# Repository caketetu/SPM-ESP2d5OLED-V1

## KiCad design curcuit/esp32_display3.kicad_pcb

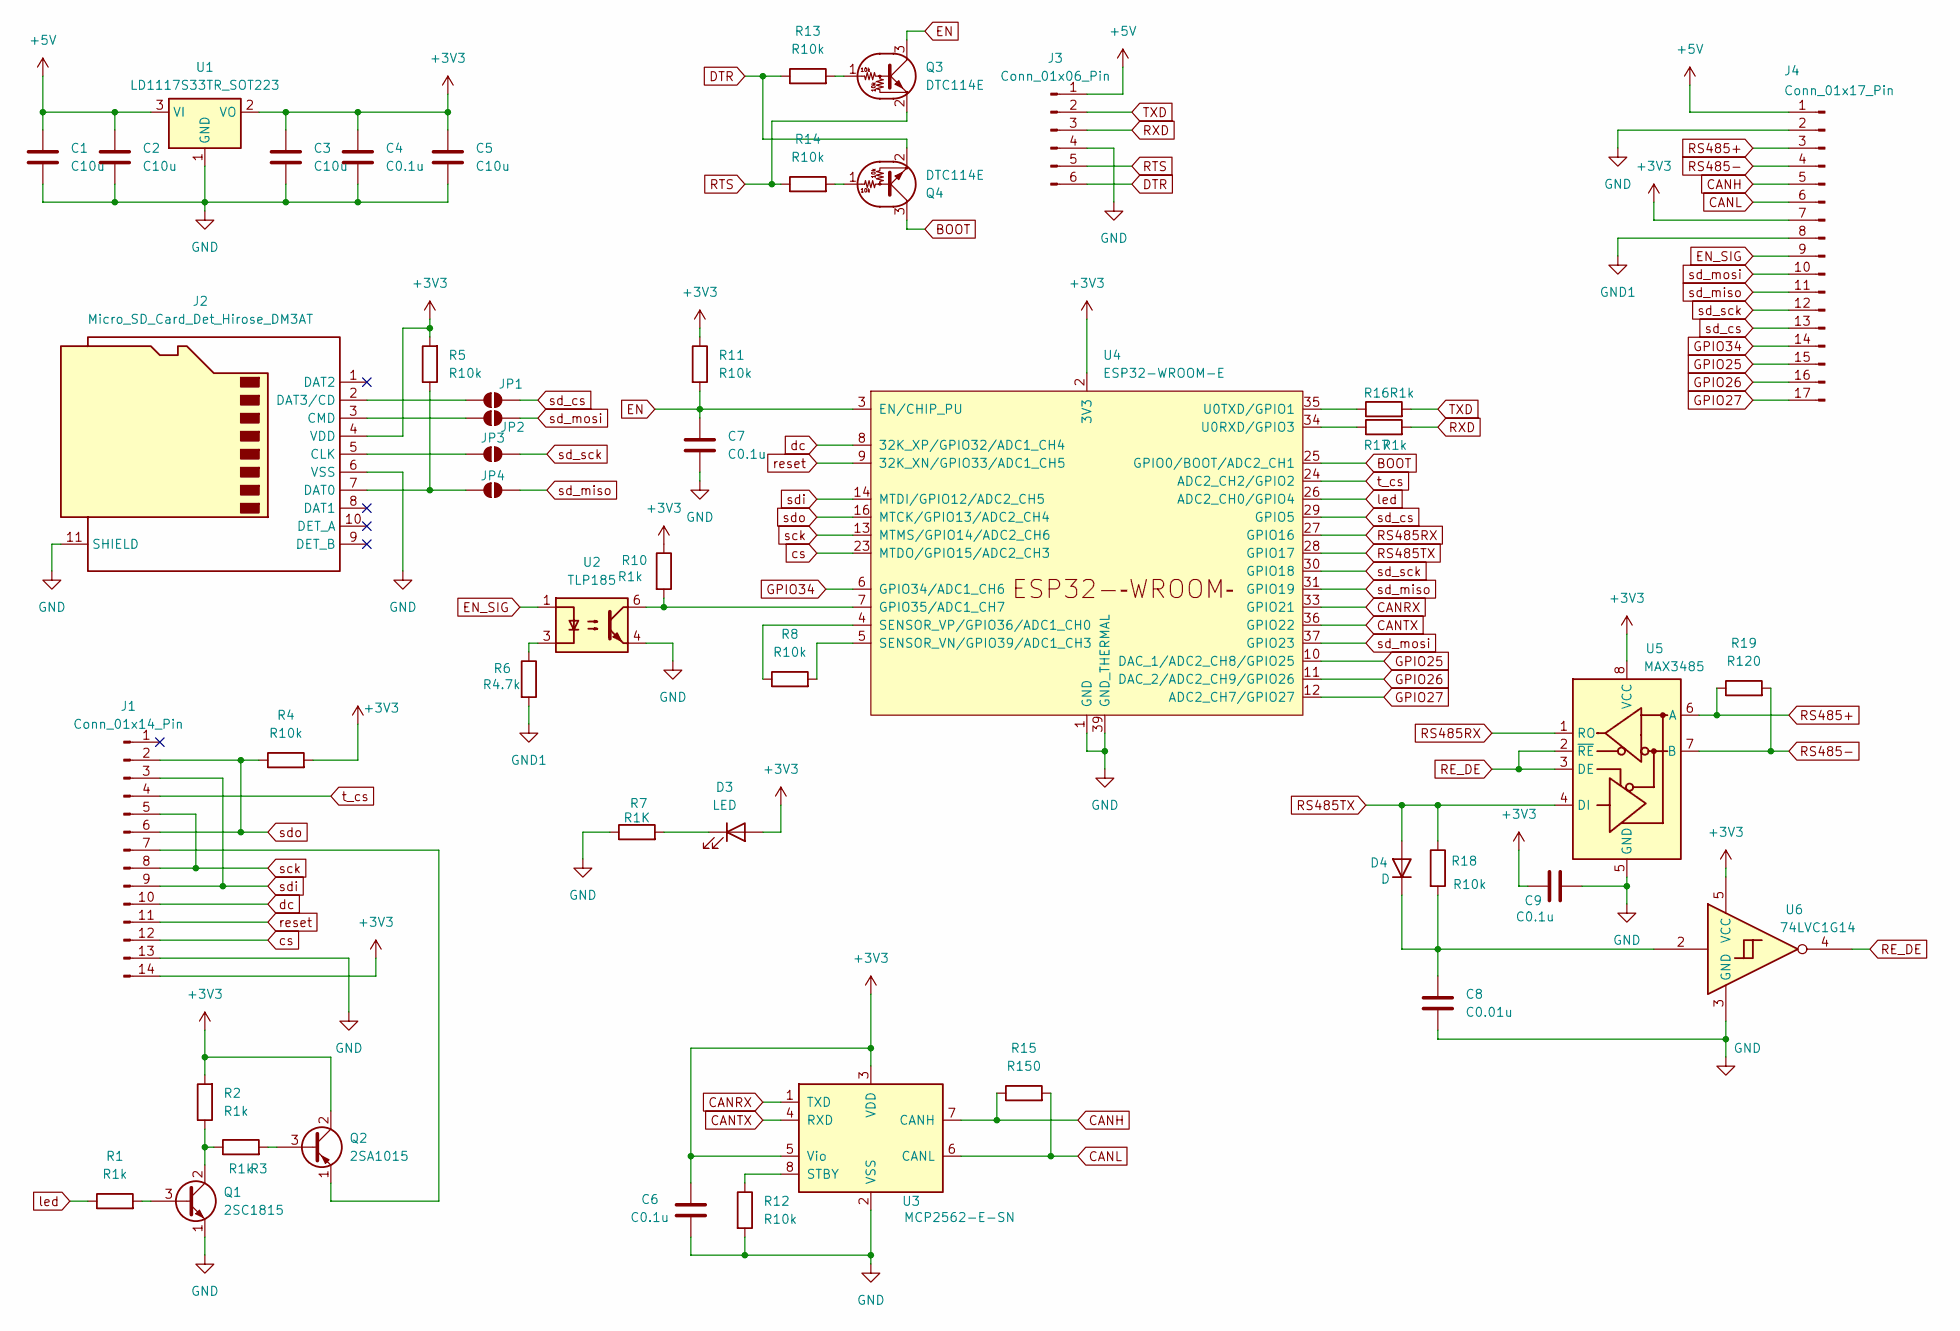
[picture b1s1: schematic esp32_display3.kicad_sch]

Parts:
C1, C2, C3, C5: C10u; C_1206_3216Metric
C4, C6, C7, C9: C0.1u; C_0603_1608Metric
C8: C0.01u; C_0805_2012Metric
D3: LED; LED_0603_1608Metric
D4: D; D_1206_3216Metric
J1: Conn_01x14_Pin; PinSocket_1x14_P2.54mm_Vertical
J2: Micro_SD_Card_Det_Hirose_DM3AT; microSD_HC_Hirose_DM3AT-SF-PEJM5
J3: Conn_01x06_Pin; JST_ZH_B6B-ZR_1x06_P1.50mm_Vertical
J4: Conn_01x17_Pin; PinHeader_1x17_P2.54mm_Vertical
JP1, JP2, JP3, JP4: SolderJumper_2_Open; SolderJumper-2_P1.3mm_Open_Pad1.0x1.5mm
Q1: 2SC1815; TO-92_Inline
Q2: 2SA1015; TO-92_Inline
Q3, Q4: DTC114E; SOT-23
R1, R2, R3, R10, R16, R17: R1k; R_0603_1608Metric
R4, R5, R8: R10k; R_1206_3216Metric
R6: R4.7k; R_0603_1608Metric
R7: R1K; R_0603_1608Metric
R11, R12, R13, R14, R18: R10k; R_0603_1608Metric
R15: R150; R_1206_3216Metric
R19: R120; R_1206_3216Metric
U1: LD1117S33TR_SOT223; SOT-223-3_TabPin2
U2: TLP185; SOIC-4_4.55x3.7mm_P2.54mm
U3: MCP2562-E-SN; SOIC-8_3.9x4.9mm_P1.27mm
U4: ESP32-WROOM-E; ESP32-WROOM-32E
U5: MAX3485; SOIC-8_3.9x4.9mm_P1.27mm
U6: 74LVC1G14; SOT-23-5

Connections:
+3V3: C3.1, C4.1, C5.1, C6.1, C9.1, D3.2 (A), J1.14, J2.4 (VDD), J4.7, Q2.2 (C), R2.2, R4.2, R5.2, R10.1, R11.1, U1.2 (VO), U3.3 (VDD), U3.5 (Vio), U4.2 (3V3), U5.8 (VCC), U6.5 (VCC)
+5V: C1.1, C2.1, J3.1, J4.1, U1.3 (VI)
BOOT: Q4.3 (C), U4.25 (GPIO0/BOOT/ADC2_CH1)
CANH: J4.5, R15.1, U3.7 (CANH)
CANL: J4.6, R15.2, U3.6 (CANL)
CANRX: U3.1 (TXD), U4.33 (GPIO21)
CANTX: U3.4 (RXD), U4.36 (GPIO22)
DTR: J3.6, Q4.2 (E), R13.1
EN: C7.1, Q3.3 (C), R11.2, U4.3 (EN/CHIP_PU)
EN_SIG: J4.9, U2.1
GND: C1.2, C2.2, C3.2, C4.2, C5.2, C6.2, C7.2, C8.2, C9.2, J1.13, J2.6 (VSS), J2.11 (SHIELD), J3.4, J4.2, Q1.1 (E), R7.1, R12.2, U1.1 (GND), U2.4, U3.2 (VSS), U4.1 (GND), U4.15 (GND), U4.38 (GND), U4.39 (GND_THERMAL), U5.5 (GND), U6.3 (GND)
GND1: J4.8, R6.2
GPIO25: J4.15, U4.10 (DAC_1/ADC2_CH8/GPIO25)
GPIO26: J4.16, U4.11 (DAC_2/ADC2_CH9/GPIO26)
GPIO27: J4.17, U4.12 (ADC2_CH7/GPIO27)
GPIO34: J4.14, U4.6 (GPIO34/ADC1_CH6)
unnamed: D3.1 (K), R7.2
unnamed: C8.1, D4.1 (K), R18.2, U6.2
unnamed: J1.7, Q2.1 (E)
unnamed: J2.5 (CLK), JP3.1 (A)
unnamed: J2.3 (CMD), JP2.1 (A)
unnamed: J2.7 (DAT0), JP4.1 (A), R5.1
unnamed: J2.2 (DAT3/CD), JP1.1 (A)
unnamed: Q1.3 (B), R1.2
unnamed: Q1.2 (C), R2.1, R3.1
unnamed: Q2.3 (B), R3.2
unnamed: Q3.1 (B), R13.2
unnamed: Q4.1 (B), R14.2
unnamed: R6.1, U2.3
unnamed: R12.1, U3.8 (STBY)
unnamed: R10.2, U2.6, U4.7 (GPIO35/ADC1_CH7)
unnamed: R8.2, U4.5 (SENSOR_VN/GPIO39/ADC1_CH3)
unnamed: R8.1, U4.4 (SENSOR_VP/GPIO36/ADC1_CH0)
unnamed: R17.1, U4.34 (U0RXD/GPIO3)
unnamed: R16.1, U4.35 (U0TXD/GPIO1)
RE_DE: U5.2 (~RE), U5.3 (DE), U6.4
RS485+: J4.3, R19.1, U5.6 (A)
RS485-: J4.4, R19.2, U5.7 (B)
RS485RX: U4.27 (GPIO16), U5.1 (RO)
RS485TX: D4.2 (A), R18.1, U4.28 (GPIO17), U5.4 (DI)
RTS: J3.5, Q3.2 (E), R14.1
RXD: J3.3, R17.2
TXD: J3.2, R16.2
cs: J1.12, U4.23 (MTDO/GPIO15/ADC2_CH3)
dc: J1.10, U4.8 (32K_XP/GPIO32/ADC1_CH4)
led: R1.1, U4.26 (ADC2_CH0/GPIO4)
reset: J1.11, U4.9 (32K_XN/GPIO33/ADC1_CH5)
sck: J1.5, J1.8, U4.13 (MTMS/GPIO14/ADC2_CH6)
sd_cs: J4.13, JP1.2 (B), U4.29 (GPIO5)
sd_miso: J4.11, JP4.2 (B), U4.31 (GPIO19)
sd_mosi: J4.10, JP2.2 (B), U4.37 (GPIO23)
sd_sck: J4.12, JP3.2 (B), U4.30 (GPIO18)
sdi: J1.3, J1.9, U4.14 (MTDI/GPIO12/ADC2_CH5)
sdo: J1.2, J1.6, R4.1, U4.16 (MTCK/GPIO13/ADC2_CH4)
t_cs: J1.4, U4.24 (ADC2_CH2/GPIO2)

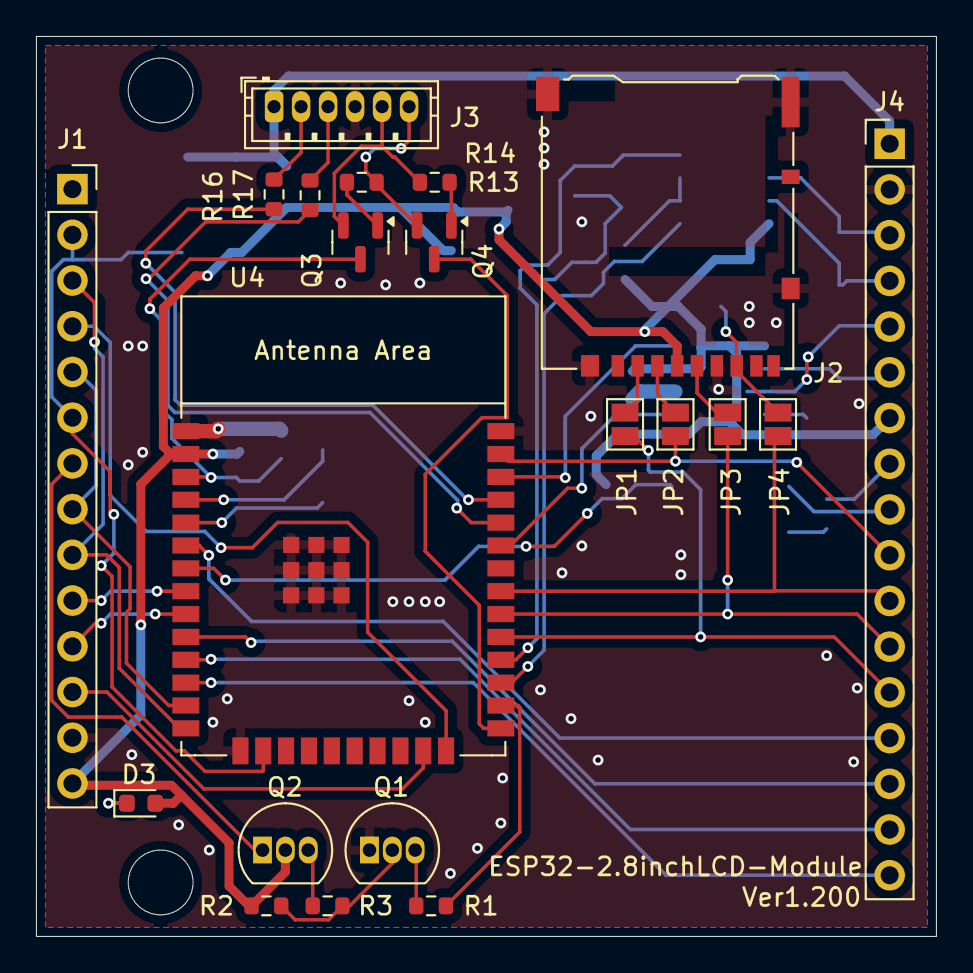
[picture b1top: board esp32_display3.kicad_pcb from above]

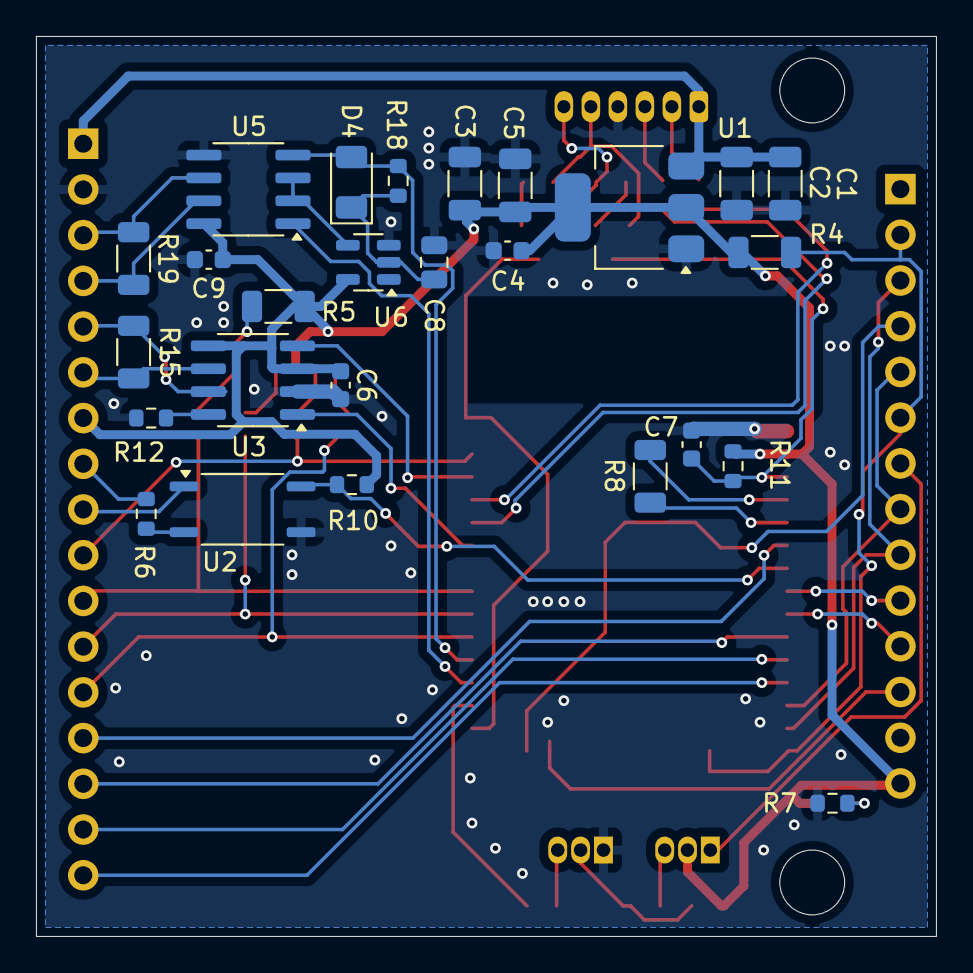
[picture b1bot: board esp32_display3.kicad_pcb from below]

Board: 2 copper layers, 50.0 x 50.0 mm, 47 parts (26 on the bottom side), 55 nets.
